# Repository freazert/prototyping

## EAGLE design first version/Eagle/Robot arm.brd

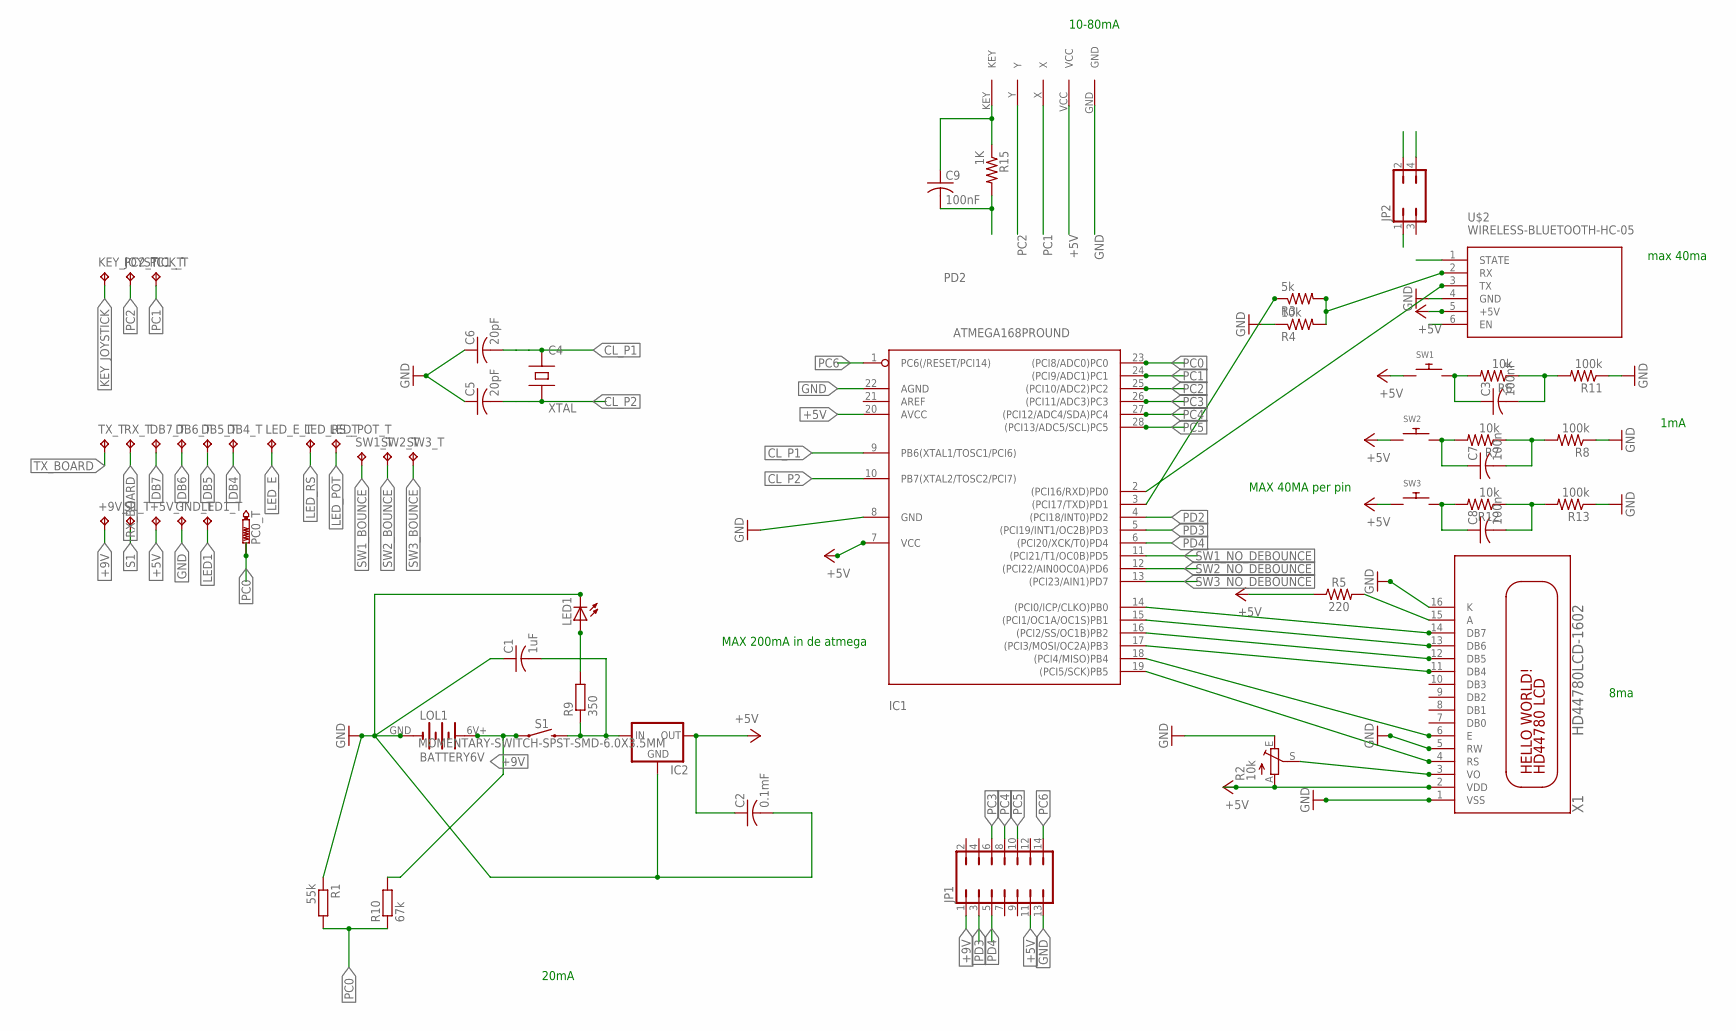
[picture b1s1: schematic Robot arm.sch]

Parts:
+5V_T, +9V_T: TPB1,27; B1,27
C1: 1uF; C025-025X050
C2: 0.1mF; C025-025X050
C3, C9: 100nF; C025-025X050
C4: XTAL; HC49UP
C5, C6: 20pF; C025-025X050
C7, C8: 100n; C025-025X050
DB4_T, DB5_T, DB6_T, DB7_T: TPB1,27; B1,27
GND_T: TPB1,27; B1,27
IC1: ATMEGA168PROUND; DIL28-3-ROUND
IC2: MCP1700INLINE; TO92-INLINE
JP1: JP7Q
JP2: JP2Q
KEY_JOYSTICK_T: TPB1,27; B1,27
LED1: LED_E; LED_1206
LED1_T: TPB1,27; B1,27
LED_E_T: TPB1,27; B1,27
LED_POT_T: TPB1,27; B1,27
LED_RS_T: TPB1,27; B1,27
LOL1: BATTERY6V; BATTERY6PACK
PC0_T: PTR1B1,27; B1,27
PC1_T, PC2_T: TPB1,27; B1,27
R1: 55k; R0805
R2: 10k; B25V
R3: 5k; 0204/5
R4, R6, R7, R12: 10k; 0204/5
R5: 220; 0603
R8, R11, R13: 100k; 0204/5
R9: 350; R0805
R10: 67k; R0805
R15: 1K; 0204/5
RX_T: TPB1,27; B1,27
S1: MOMENTARY-SWITCH-SPST-SMD-6.0X3.5MM; TACTILE_SWITCH_SMD_6.0X3.5MM
S1_T: TPB1,27; B1,27
SW1, SW2, SW3: SWITCH_PUSHBUTTONSOFTTOUCHSMD_SJ; PUSHBUTTON_SMD_SJ
SW1_T, SW2_T, SW3_T: TPB1,27; B1,27
TX_T: TPB1,27; B1,27
U$1: JOYSTICK
U$2: WIRELESS-BLUETOOTH-HC-05
X1: HD44780LCD-1602; LCD1602

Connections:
+5V: +5V_T.TP, C2.1, IC1.7 (VCC), IC1.20 (AVCC), IC2.3 (OUT), JP1.11, R2.A, R5.1, SW1.P$1, SW2.P$1, SW3.P$1, U$1.VCC, U$2.5 (+5V), X1.2 (VDD)
+9V: +9V_T.TP, JP1.1, LOL1.6V+ (6V), R10.2, S1.1
CL_P1: C4.1 (A), C6.2, IC1.9 (PB6(XTAL1/TOSC1/PCI6))
CL_P2: C4.2 (B), C5.2, IC1.10 (PB7(XTAL2/TOSC2/PCI7))
DB4: DB4_T.TP, IC1.17 ((PCI3/MOSI/OC2A)PB3), X1.11 (DB4)
DB5: DB5_T.TP, IC1.16 ((PCI2/SS/OC1B)PB2), X1.12 (DB5)
DB6: DB6_T.TP, IC1.15 ((PCI1/OC1A/OC1S)PB1), X1.13 (DB6)
DB7: DB7_T.TP, IC1.14 ((PCI0/ICP/CLKO)PB0), X1.14 (DB7)
EN: JP2.4, U$2.6 (EN)
GND: C1.1, C2.2, C5.1, C6.1, GND_T.TP, IC1.8 (GND), IC1.22 (AGND), IC2.1 (GND), JP1.13, JP2.1, LED1.C, LOL1.GND, R1.1, R2.E, R4.1, R8.1, R11.1, R13.1, U$1.GND, U$2.4 (GND), X1.1 (VSS), X1.5 (RW), X1.16 (K)
KEY_JOYSTICK: C9.1, KEY_JOYSTICK_T.TP, R15.1, U$1.KEY
LED1: LED1.A, LED1_T.TP, R9.2
LED_E: IC1.18 ((PCI4/MISO)PB4), LED_E_T.TP, X1.6 (E)
LED_POT: LED_POT_T.TP, R2.S, X1.3 (VO)
LED_RS: IC1.19 ((PCI5/SCK)PB5), LED_RS_T.TP, X1.4 (RS)
unnamed: R5.2, X1.15 (A)
PC0: IC1.23 ((PCI8/ADC0)PC0), PC0_T.TP, R1.2, R10.1
PC1: IC1.24 ((PCI9/ADC1)PC1), PC1_T.TP, U$1.X
PC2: IC1.25 ((PCI10/ADC2)PC2), PC2_T.TP, U$1.Y
PC3: IC1.26 ((PCI11/ADC3)PC3), JP1.6
PC4: IC1.27 ((PCI12/ADC4/SDA)PC4), JP1.8
PC5: IC1.28 ((PCI13/ADC5/SCL)PC5), JP1.10
PC6: IC1.1 (PC6(/RESET/PCI14)), JP1.14
PD2: C9.2, IC1.4 ((PCI18/INT0)PD2), R15.2
PD3: IC1.5 ((PCI19/INT1/OC2B)PD3), JP1.3
PD4: IC1.6 ((PCI20/XCK/T0)PD4), JP1.5
RX: R3.2, R4.2, U$2.2 (RX)
RX_BOARD: IC1.2 ((PCI16/RXD)PD0), RX_T.TP, U$2.3 (TX)
S1: C1.2, IC2.2 (IN), R9.1, S1.2, S1_T.TP
STATE: JP2.2, U$2.1 (STATE)
SW1_BOUNCE: C3.1, R6.2, SW1.P$2, SW1_T.TP
SW1_NO_DEBOUNCE: C3.2, IC1.11 ((PCI21/T1/OC0B)PD5), R6.1, R11.2
SW2_BOUNCE: C7.1, R7.2, SW2.P$2, SW2_T.TP
SW2_NO_DEBOUNCE: C7.2, IC1.12 ((PCI22/AIN0OC0A)PD6), R7.1, R8.2
SW3_BOUNCE: C8.1, R12.2, SW3.P$2, SW3_T.TP
SW3_NO_DEBOUNCE: C8.2, IC1.13 ((PCI23/AIN1)PD7), R12.1, R13.2
TX_BOARD: IC1.3 ((PCI17/TXD)PD1), R3.1, TX_T.TP

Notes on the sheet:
max 40ma
8ma
1mA
10-80mA
20mA
MAX 40MA per pin
MAX 200mA in de atmega

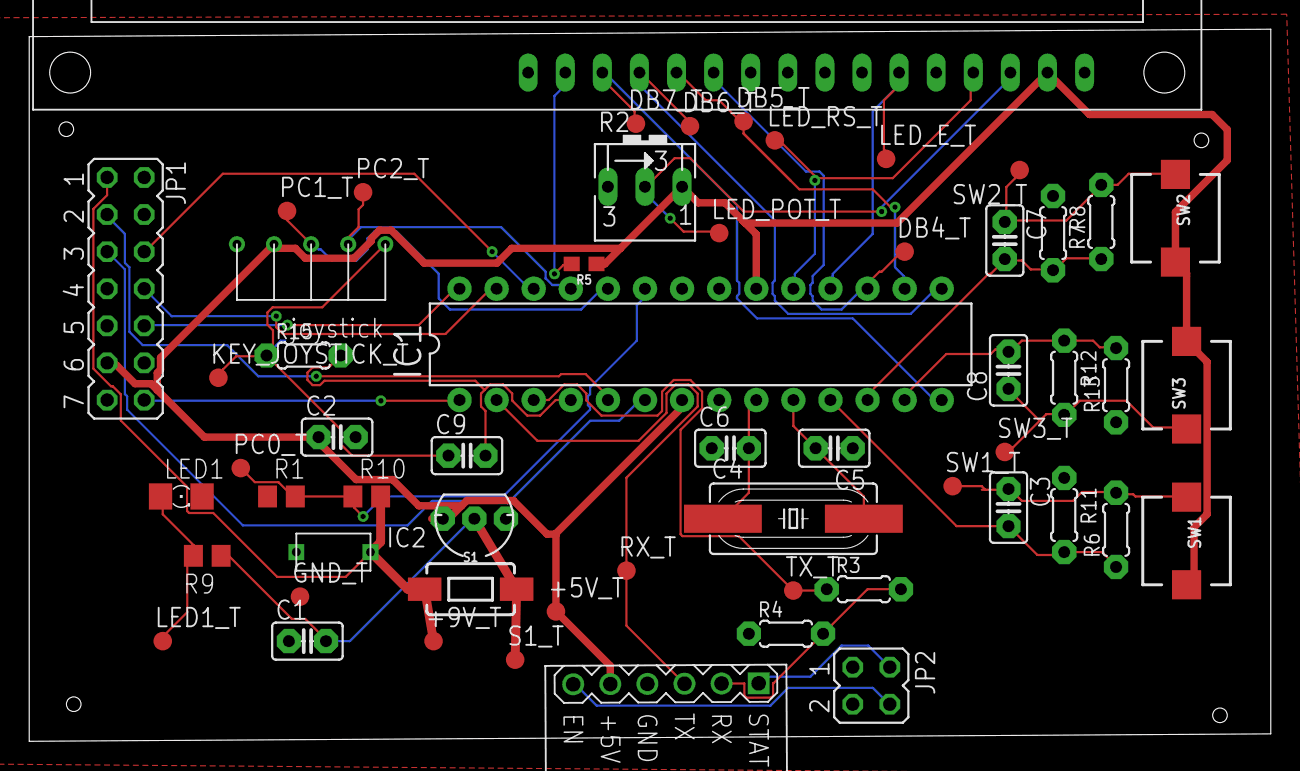
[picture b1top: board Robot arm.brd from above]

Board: 2 copper layers, 85.0 x 48.8 mm, 57 parts (0 on the bottom side), 37 nets.

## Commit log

2018-10-17 to git

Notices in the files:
parts and their libraries:
SparkFun-Resistors: Licensing: Creative Commons ShareAlike 4.0 International - https://creativecommons.org/licenses/by-sa/4.0
diy-modules: Released under the Creative Commons Attribution 4.0 International License: http://creativecommons.org/licenses/by/4.0
